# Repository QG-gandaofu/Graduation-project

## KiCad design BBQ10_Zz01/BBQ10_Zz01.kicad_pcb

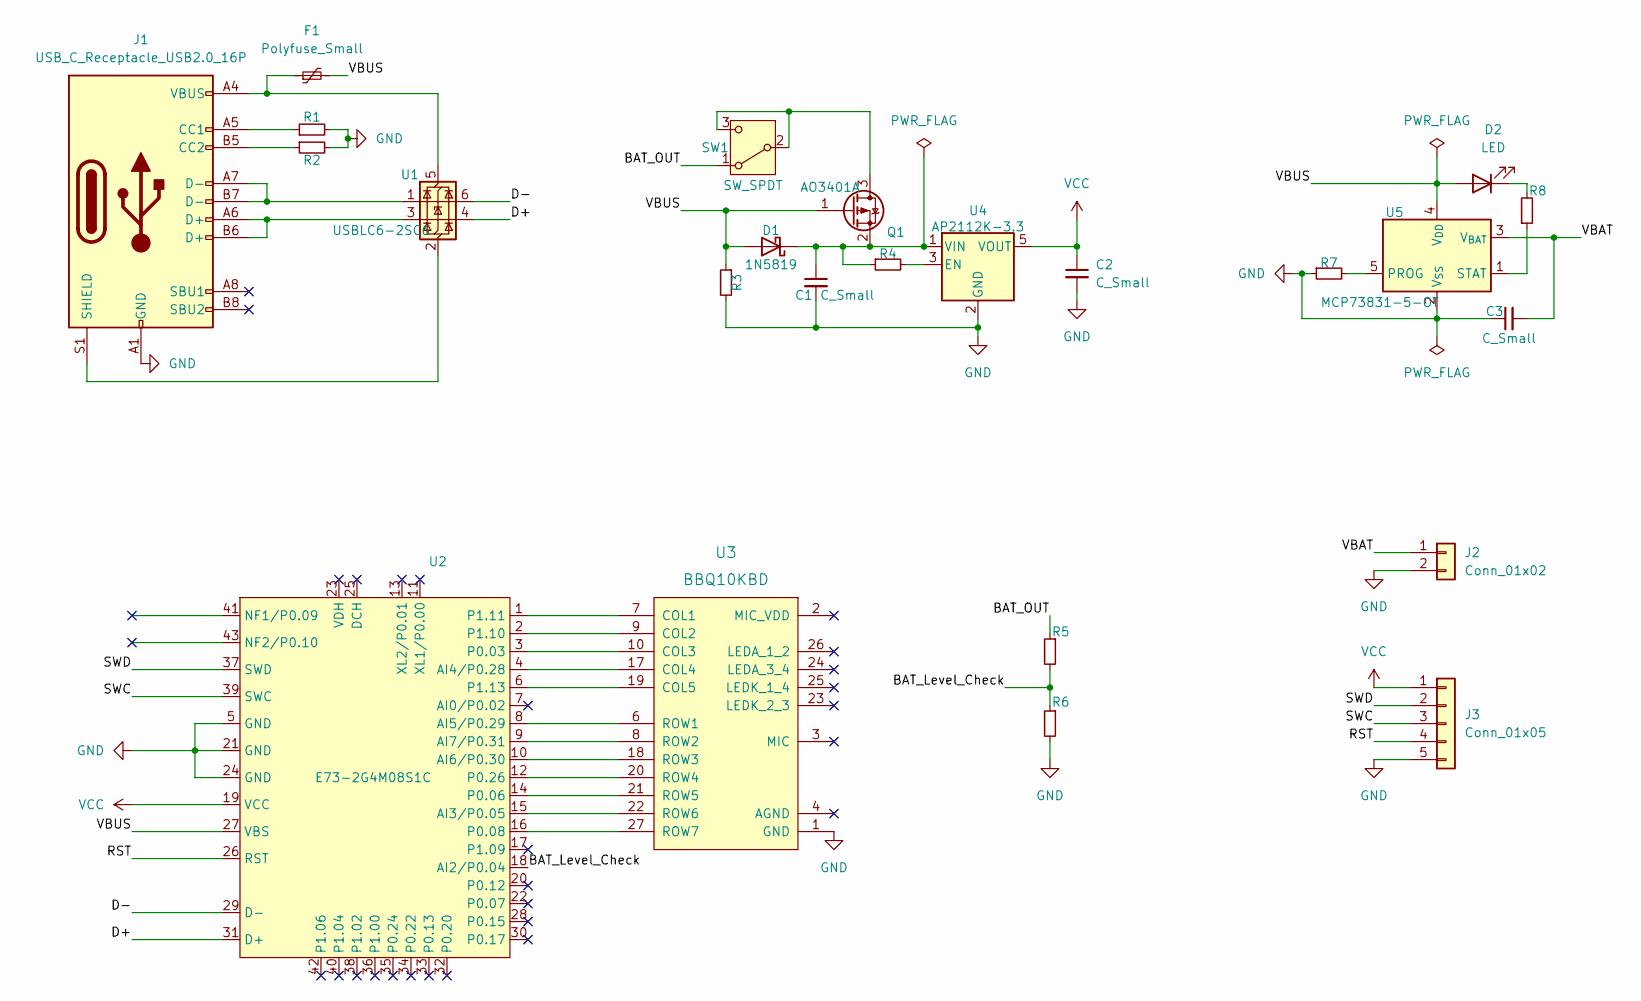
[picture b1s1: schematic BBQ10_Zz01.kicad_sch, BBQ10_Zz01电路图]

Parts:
C1, C2, C3: C_Small; C_0603_1608Metric_Pad1.08x0.95mm_HandSolder
D1: 1N5819; D_0603_1608Metric_Pad1.05x0.95mm_HandSolder
D2: LED; LED_0603_1608Metric_Pad1.05x0.95mm_HandSolder
F1: Polyfuse_Small; Fuse_0603_1608Metric
J1: USB_C_Receptacle_USB2.0_16P; USB_C_Receptacle_GCT_USB4105-xx-A_16P_TopMnt_Horizontal
J2: Conn_01x02; PinHeader_1x02_P2.54mm_Horizontal
J3: Conn_01x05; PinHeader_1x05_P2.54mm_Horizontal
Q1: AO3401A; SOT-23
R1, R2, R3, R4, R5, R6, R7, R8: R_Small; R_0603_1608Metric_Pad0.98x0.95mm_HandSolder
SW1: SW_SPDT
U1: USBLC6-2SC6; SOT-23-6
U2: E73-2G4M08S1C; E73(2G4M08S1C)
U3: BBQ10KBD; BM14B(0.8)-24DS-0.4V(53)
U4: AP2112K-3.3; SOT-23-5
U5: MCP73831-5-OT; SOT-23-5

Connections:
/BAT_Level_Check: R5.2, R6.1, U2.18 (AI2/P0.04)
/BAT_OUT: R5.1, SW1.1 (A)
/D+: U1.4 (I/O2), U2.31 (D+)
/D-: U1.6 (I/O1), U2.29 (D-)
/RST: J3.4, U2.26 (RST)
/SWC: J3.3, U2.39 (SWC)
/SWD: J3.2, U2.37 (SWD)
/VBAT: C3.2, J2.1, U5.3 (V_{BAT})
/VBUS: D1.2 (A), D2.2 (A), F1.2, Q1.1 (G), R3.1, U2.27 (VBS), U5.4 (V_{DD})
GND: C1.2, C2.2, C3.1, J1.A1 (GND), J1.A12 (GND), J1.B1 (GND), J1.B12 (GND), J2.2, J3.5, R1.2, R2.2, R3.2, R6.2, R7.1, U2.5 (GND), U2.21 (GND), U2.24 (GND), U3.1 (GND), U3.5 (GND), U3.11 (GND), U3.12 (GND), U3.13 (GND), U3.14 (GND), U3.15 (GND), U3.16 (GND), U3.28 (GND), U4.2 (GND), U5.2 (V_{SS})
unnamed: C1.1, D1.1 (K), Q1.2 (S), R4.1, U4.1 (VIN)
unnamed: D2.1 (K), R8.2
unnamed: J1.A5 (CC1), R1.1
unnamed: J1.B5 (CC2), R2.1
unnamed: J1.A6 (D+), J1.B6 (D+), U1.3 (I/O2)
unnamed: J1.A7 (D-), J1.B7 (D-), U1.1 (I/O1)
unnamed: J1.S1 (SHIELD), U1.2 (GND)
unnamed: Q1.3 (D), SW1.2 (B), SW1.3 (C)
unnamed: F1.1, J1.A4 (VBUS), J1.A9 (VBUS), J1.B4 (VBUS), J1.B9 (VBUS), U1.5 (VBUS)
unnamed: U2.15 (AI3/P0.05), U3.22 (ROW6)
unnamed: U2.4 (AI4/P0.28), U3.17 (COL4)
unnamed: U2.8 (AI5/P0.29), U3.6 (ROW1)
unnamed: U2.10 (AI6/P0.30), U3.18 (ROW3)
unnamed: U2.9 (AI7/P0.31), U3.8 (ROW2)
unnamed: U2.3 (P0.03), U3.10 (COL3)
unnamed: U2.14 (P0.06), U3.21 (ROW5)
unnamed: U2.16 (P0.08), U3.27 (ROW7)
unnamed: U2.12 (P0.26), U3.20 (ROW4)
unnamed: U2.2 (P1.10), U3.9 (COL2)
unnamed: U2.1 (P1.11), U3.7 (COL1)
unnamed: U2.6 (P1.13), U3.19 (COL5)
unnamed: R4.2, U4.3 (EN)
unnamed: R7.2, U5.5 (PROG)
unnamed: R8.1, U5.1 (STAT)
VCC: C2.1, J3.1, U2.19 (VCC), U4.5 (VOUT)

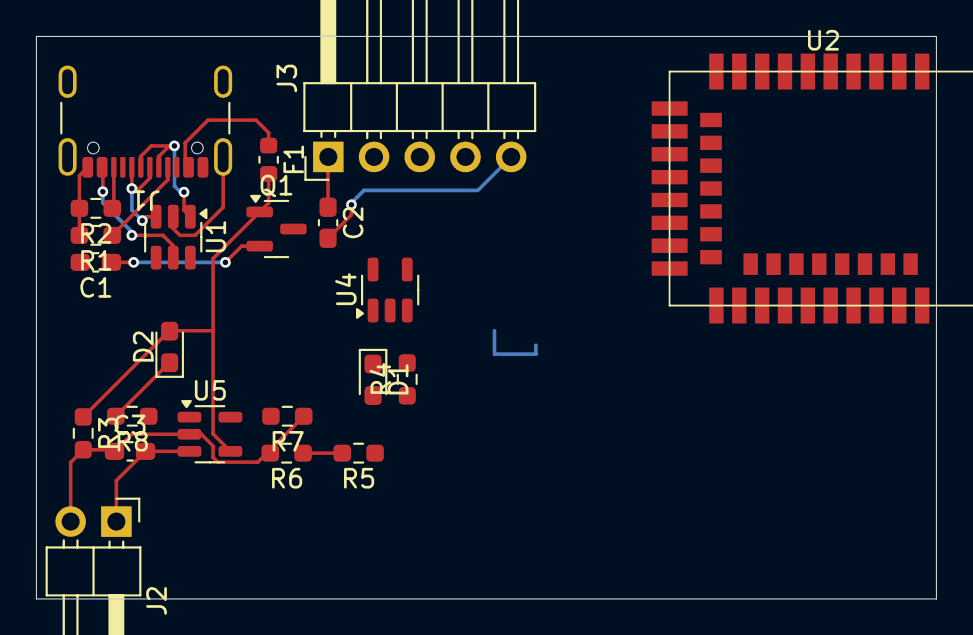
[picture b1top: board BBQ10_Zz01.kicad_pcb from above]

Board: 2 copper layers, 50.0 x 31.2 mm, 23 parts (1 on the bottom side), 33 nets.

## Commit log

2024-08-15 论文文件创建
2024-09-17 sch-V1,done
2024-09-20 添加了一些备注，瞎整了一个PCB
2024-10-25 开题报告预备更新
    去除某些不必要git文件，整理重新开始
2024-10-25 更新了一点点任务书
2024-11-10 完善了开题报告和任务书
2025-01-13 重置环境
2025-02-17 update resource
